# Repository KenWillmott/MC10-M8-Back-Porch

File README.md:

# MC10-M8-Back-Porch
Flash ROM and serial interface for TRS-80 MC-10

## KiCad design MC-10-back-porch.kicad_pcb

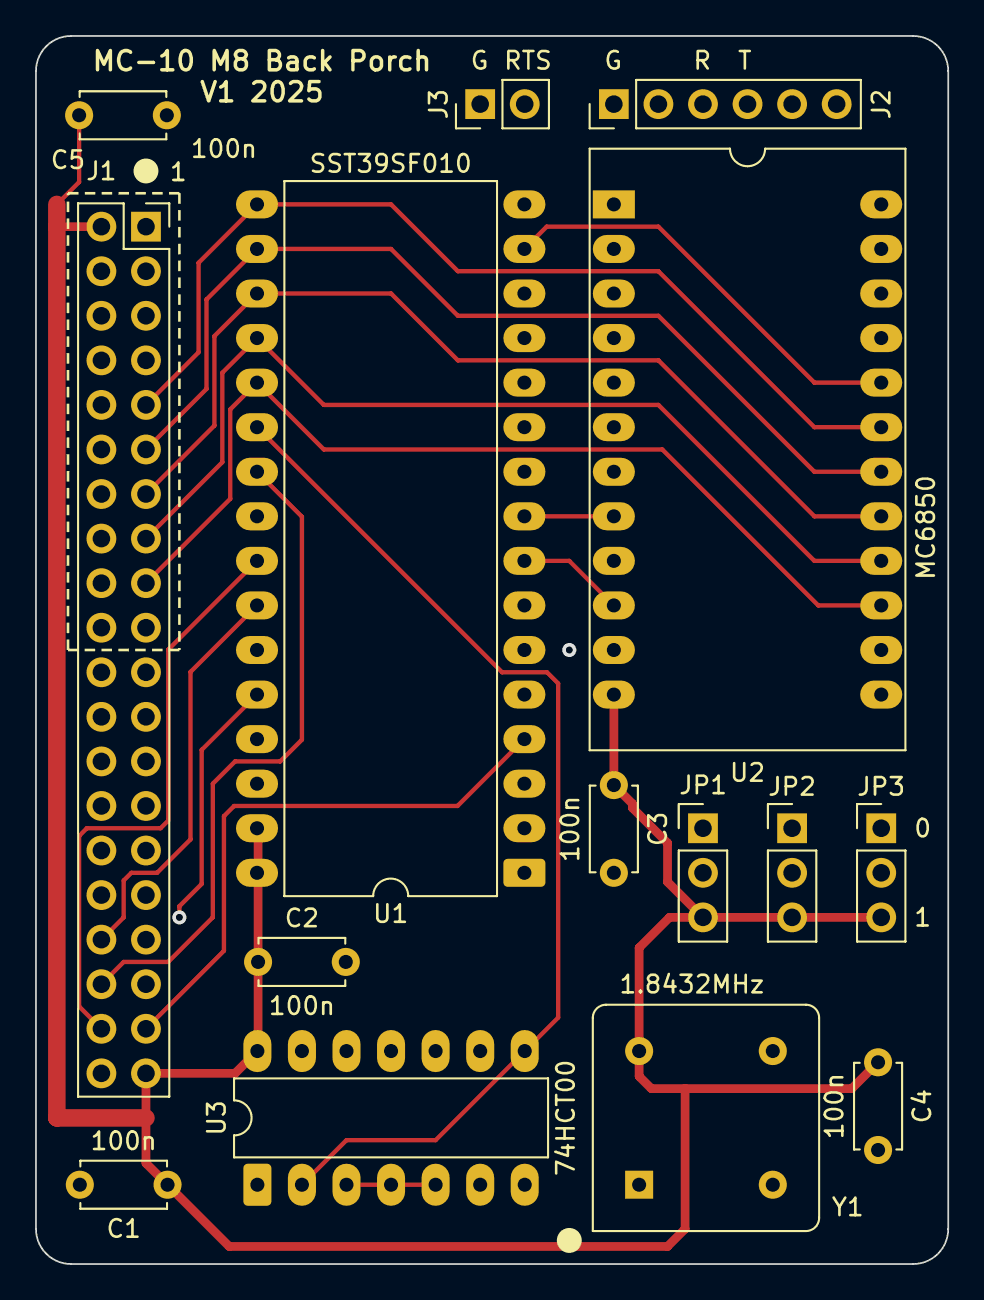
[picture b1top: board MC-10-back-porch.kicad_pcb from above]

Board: 4 copper layers, 52.0 x 70.0 mm, 15 parts (0 on the bottom side), 41 nets.

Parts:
C1, C2, C3, C4, C5: 100n; C_Disc_D4.7mm_W2.5mm_P5.00mm
J1: Conn_02x20_Odd_Even; PinSocket_2x20_P2.54mm_Vertical
J2: Conn_01x06_Pin; PinHeader_1x06_P2.54mm_Vertical
J3: Conn_01x02_Pin; PinHeader_1x02_P2.54mm_Vertical
JP1, JP2, JP3: Jumper_3_Bridged12; PinHeader_1x03_P2.54mm_Vertical
U1: SST39SF010; DIP-32_W15.24mm_LongPads
U2: MC6850; DIP-24_18.0mmx34.29mm_W15.24mm_LongPads
U3: 74HCT00; DIP-14_W7.62mm_LongPads
Y1: 1.8432MHz; Oscillator_DIP-8

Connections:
/A0: J1.4, U1.12 (A0), U2.11 (RS)
/A1: J1.6, U1.11 (A1)
/A2: J1.8, U1.10 (A2)
/A5: J1.26, U1.7 (A5)
/A6: J1.28, U1.6 (A6)
/A7: J1.30, U1.5 (A7)
/A8: J1.32, U1.27 (A8)
/A9: J1.34, U1.26 (A9)
/A10: J1.36, U1.23 (A10)
/A11: J1.38, U1.25 (A11)
/A12: J1.37, U1.4 (A12)
/A13: J1.35, U1.28 (A13)
/A14: J1.33, U3.9
/A15: J1.31, U3.10
/D0: J1.3, U1.13 (D0), U2.22 (D0)
/D1: J1.5, U1.14 (D1), U2.21 (D1)
/D2: J1.7, U1.15 (D2), U2.20 (D2)
/D3: J1.9, U1.17 (D3), U2.19 (D3)
/D4: J1.11, U1.18 (D4), U2.18 (D4)
/D5: J1.13, U1.19 (D5), U2.17 (D5)
/D6: J1.15, U1.20 (D6), U2.16 (D6)
/D7: J1.17, U1.21 (D7), U2.15 (D7)
/RA14: JP1.2 (C), U1.29 (A14)
/RA15: JP2.2 (C), U1.3 (A15)
/RA16: JP3.2 (C), U1.2 (A16)
/RXD: J2.3, U2.2 (Rx_Data)
/TXD: J2.4, U2.6 (Tx_Data)
A3: J1.10, U1.9 (A3), U2.8 (CS0)
A4: J1.12, U1.8 (A4), U2.10 (CS1)
BSEL0*: J1.19, U2.9 (CS2), U3.1
DIS*: J1.21, U3.6
E: J1.14, U2.14 (E), U3.13
GND: C1.2, C2.2, C3.2, C4.2, C5.2, J1.1, J1.40, J2.1, J3.1, JP1.1 (A), JP2.1 (A), JP3.1 (A), U1.16 (GND), U2.1 (VSS), U2.23 (~DCD), U2.24 (~CTS), U3.7 (GND), Y1.4 (GND)
IRQ*: J1.20, U2.7 (~IRQ)
unnamed: J3.2, U2.5 (~RTS)
unnamed: U1.22 (CE), U3.2, U3.8
unnamed: U1.24 (OE), U3.11
unnamed: U2.3 (Rx_CLK), U2.4 (Tx_CLK), Y1.5 (OUT)
unnamed: U3.3, U3.4, U3.5
R/W*: J1.16, U2.13 (R/~W), U3.12
VCC: C1.1, C2.1, C3.1, C4.1, C5.1, J1.2, J1.39, JP1.3 (B), JP2.3 (B), JP3.3 (B), U1.31 (PGM), U1.32 (VCC), U2.12 (VCC), U3.14 (VCC), Y1.8 (Vcc)

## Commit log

2025-09-07 add schematic
2025-09-07 add Kbug monitor assembly source
2025-09-07 add Kbug binary 16k partition
